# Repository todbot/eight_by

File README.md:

# eight_by

An 8-knob + 8 buttons + eight RGB LEDs board,<br/>
all controllable with only 8 pins

Pot options:

- 9mm Song Hui trimmer pots B10K - [synthcube](https://synthcube.com/cart/parts/potentiometers-and-trimpots/song-huei-9mm-panel-trim-pot-short)
- Just about any other 9mm pot

Buttons are: 
- 12mm tact (LCSC C561260)

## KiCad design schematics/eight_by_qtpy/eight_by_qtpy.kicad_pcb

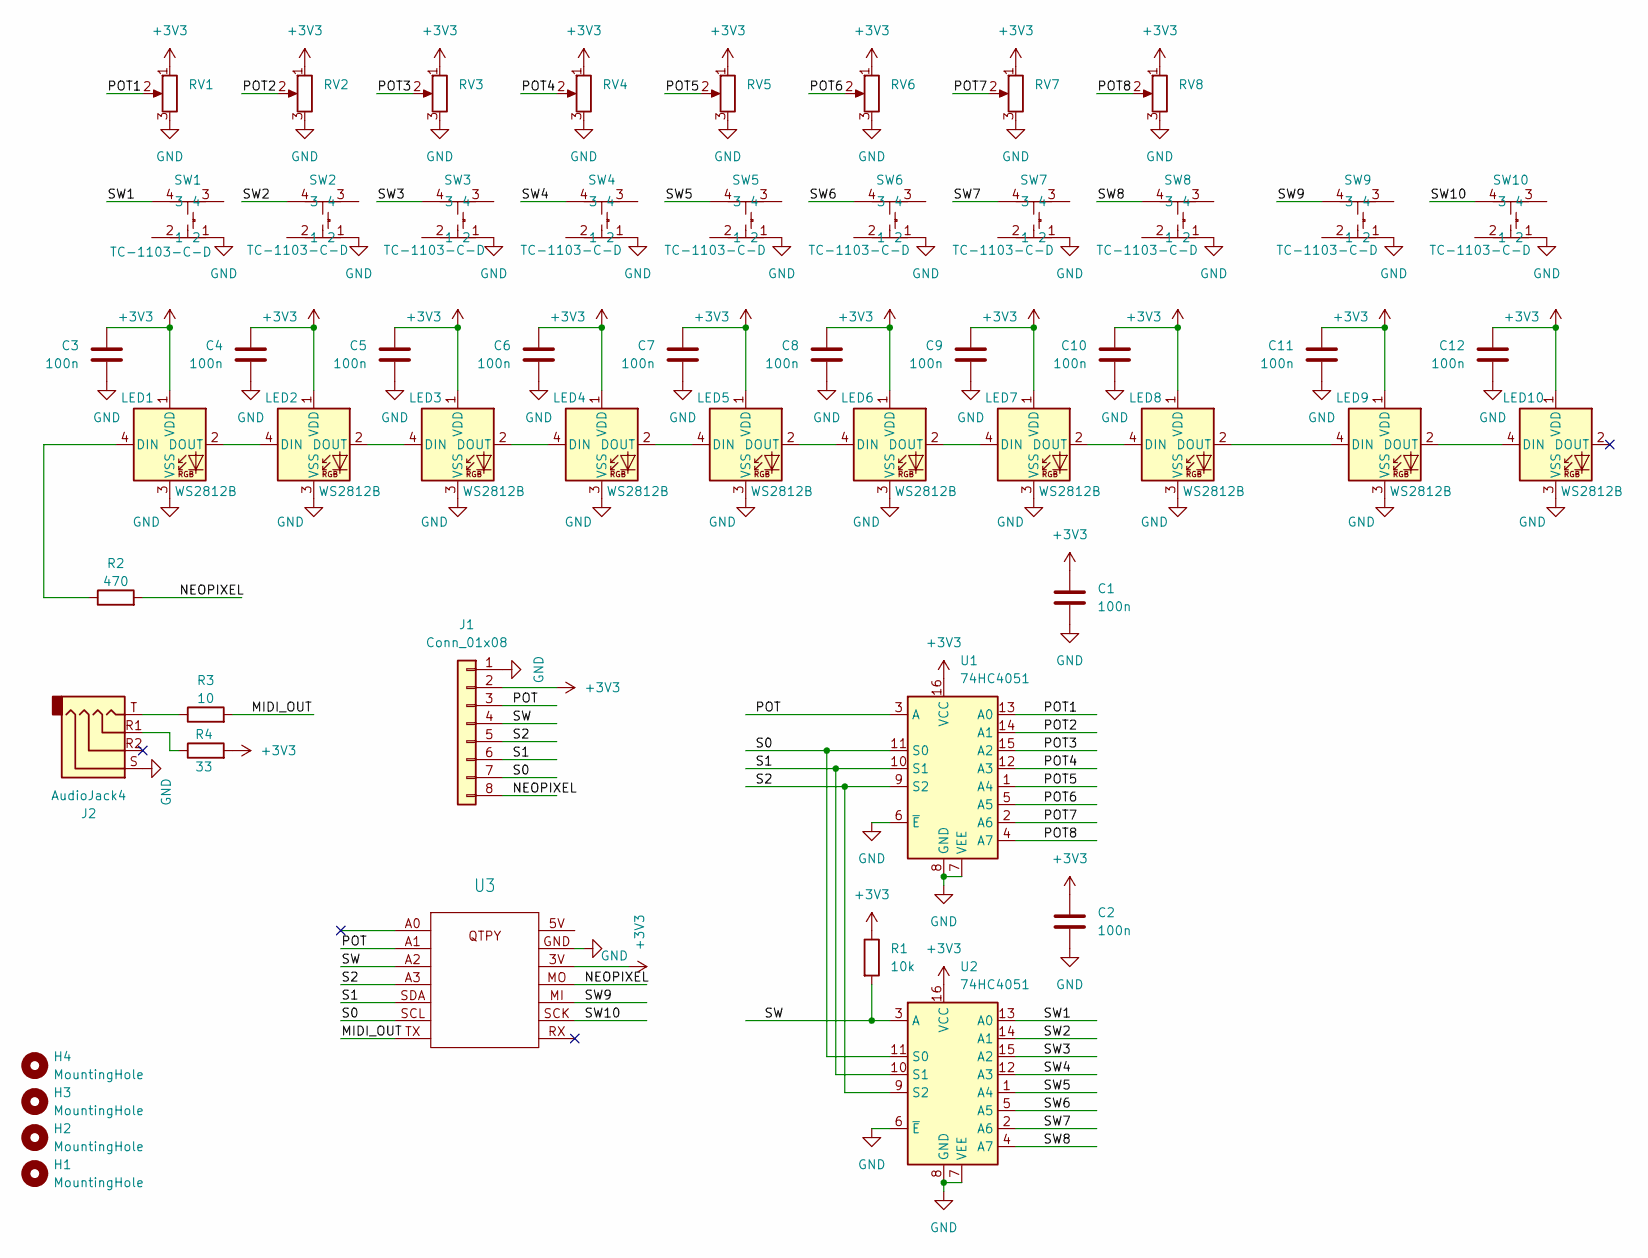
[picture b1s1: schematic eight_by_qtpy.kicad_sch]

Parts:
C1, C2, C3, C4, C5, C6, C7, C8, C9, C10, C11, C12: 100n; C_0603_1608Metric
H1, H2, H3, H4: MountingHole; MountingHole_2.5mm
J1: Conn_01x08; PinHeader_1x08_P2.54mm_Vertical
J2: AudioJack4; Jack_3.5mm_PJ320D_Horizontal
LED1, LED2, LED3, LED4, LED5, LED6, LED7, LED8, LED9, LED10: WS2812B; LED_WS2812B-Mini_PLCC4_3.5x3.5mm
R1: 10k; R_0603_1608Metric
R2: 470; R_0603_1608Metric
R3: 10; R_0603_1608Metric
R4: 33; R_0603_1608Metric
RV1, RV2, RV3, RV4, RV5, RV6, RV7, RV8: R_Potentiometer; Potentiometer_Alps_RK09K_Single_Vertical
SW1, SW2, SW3, SW4, SW5, SW6, SW7, SW8, SW9, SW10: TC-1103-C-D; SW-TH_4P-L12.0-W12.0-P5.00-LS12.5; LCSC Part C561260
U1, U2: 74HC4051; SOIC-16_3.9x9.9mm_P1.27mm
U3: QTPY_TH_HEADERSOCKET

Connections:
+3V3: C1.1, C2.1, C3.1, C4.1, C5.1, C6.1, C7.1, C8.1, C9.1, C10.1, C11.1, C12.1, J1.2, LED1.1 (VDD), LED2.1 (VDD), LED3.1 (VDD), LED4.1 (VDD), LED5.1 (VDD), LED6.1 (VDD), LED7.1 (VDD), LED8.1 (VDD), LED9.1 (VDD), LED10.1 (VDD), R1.1, R4.2, RV1.1, RV2.1, RV3.1, RV4.1, RV5.1, RV6.1, RV7.1, RV8.1, U1.16 (VCC), U2.16 (VCC), U3.3V
/MIDI_OUT: R3.2, U3.TX
/NEOPIXEL: J1.8, R2.2, U3.MO
/POT: J1.3, U1.3 (A), U3.A1 (9)
/POT1: RV1.2, U1.13 (A0)
/POT2: RV2.2, U1.14 (A1)
/POT3: RV3.2, U1.15 (A2)
/POT4: RV4.2, U1.12 (A3)
/POT5: RV5.2, U1.1 (A4)
/POT6: RV6.2, U1.5 (A5)
/POT7: RV7.2, U1.2 (A6)
/POT8: RV8.2, U1.4 (A7)
/S0: J1.7, U1.11 (S0), U2.11 (S0), U3.SCL
/S1: J1.6, U1.10 (S1), U2.10 (S1), U3.SDA
/S2: J1.5, U1.9 (S2), U2.9 (S2), U3.A3
/SW: J1.4, R1.2, U2.3 (A), U3.A2
/SW1: SW1.4, U2.13 (A0)
/SW2: SW2.4, U2.14 (A1)
/SW3: SW3.4, U2.15 (A2)
/SW4: SW4.4, U2.12 (A3)
/SW5: SW5.4, U2.1 (A4)
/SW6: SW6.4, U2.5 (A5)
/SW7: SW7.4, U2.2 (A6)
/SW8: SW8.4, U2.4 (A7)
/SW9: SW9.4, U3.MI
/SW10: SW10.4, U3.SCK
GND: C1.2, C2.2, C3.2, C4.2, C5.2, C6.2, C7.2, C8.2, C9.2, C10.2, C11.2, C12.2, J1.1, J2.S, LED1.3 (VSS), LED2.3 (VSS), LED3.3 (VSS), LED4.3 (VSS), LED5.3 (VSS), LED6.3 (VSS), LED7.3 (VSS), LED8.3 (VSS), LED9.3 (VSS), LED10.3 (VSS), RV1.3, RV2.3, RV3.3, RV4.3, RV5.3, RV6.3, RV7.3, RV8.3, SW1.1, SW2.1, SW3.1, SW4.1, SW5.1, SW6.1, SW7.1, SW8.1, SW9.1, SW10.1, U1.6 (~E), U1.7 (VEE), U1.8 (GND), U2.6 (~E), U2.7 (VEE), U2.8 (GND), U3.GND (14)
unnamed: J2.R1, R4.1
unnamed: J2.T, R3.1
unnamed: LED1.4 (DIN), R2.1
unnamed: LED1.2 (DOUT), LED2.4 (DIN)
unnamed: LED2.2 (DOUT), LED3.4 (DIN)
unnamed: LED3.2 (DOUT), LED4.4 (DIN)
unnamed: LED4.2 (DOUT), LED5.4 (DIN)
unnamed: LED5.2 (DOUT), LED6.4 (DIN)
unnamed: LED6.2 (DOUT), LED7.4 (DIN)
unnamed: LED7.2 (DOUT), LED8.4 (DIN)
unnamed: LED8.2 (DOUT), LED9.4 (DIN)
unnamed: LED9.2 (DOUT), LED10.4 (DIN)

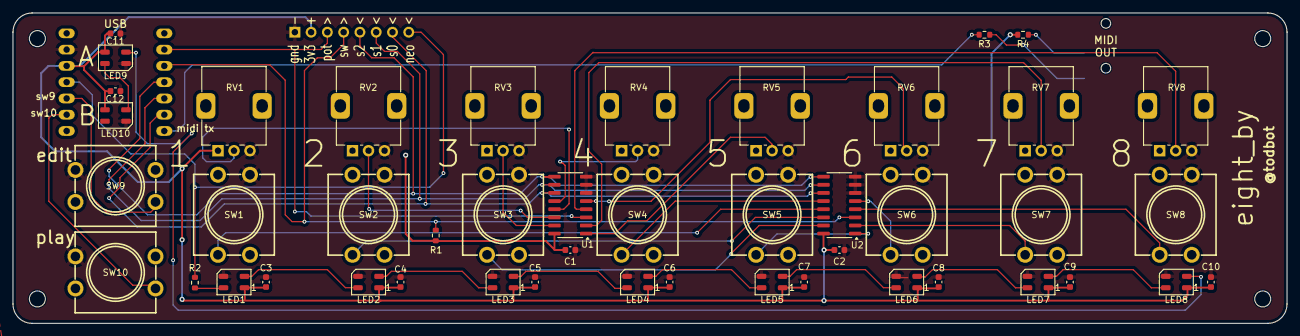
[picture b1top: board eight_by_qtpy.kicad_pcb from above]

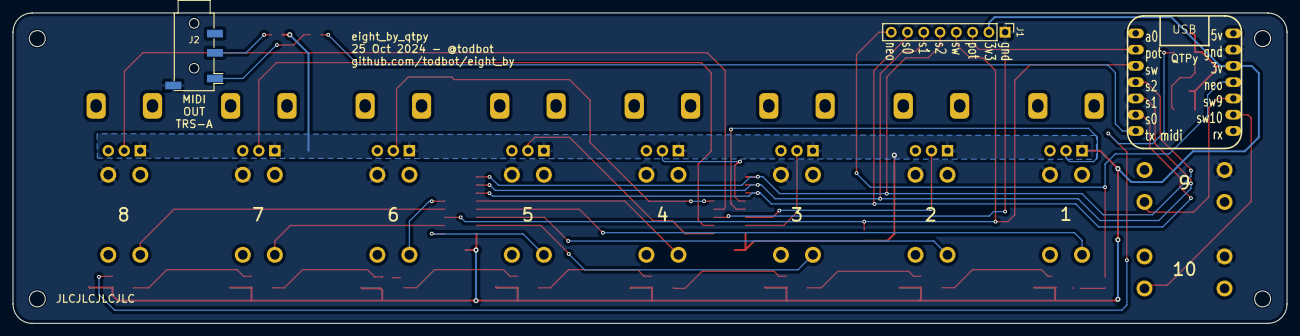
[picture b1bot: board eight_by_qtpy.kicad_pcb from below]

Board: 2 copper layers, 198.9 x 48.4 mm, 53 parts (3 on the bottom side), 39 nets.

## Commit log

2024-05-30 first
2024-06-27 pcb silkscren update
2024-10-23 add render
2024-10-24 eight_by_qtpy idea
2024-10-24 add two extra buttons & LEDs if using a QTpy
2024-10-26 clean up
2024-11-14 rethinking eight_by_qtpy
2024-11-23 new silkscreen
2024-11-24 refactor eight_by_qtpy to use 12mm switches instead of std 6mm tact
2024-11-25 clea up eight_by_qtpy refactor layout
2024-11-25 clean up eight_by_qtpy refactor layout
2024-11-26 files as sent to fab
2025-06-04 add sch pdf
2025-06-04 add sch png
2025-06-04 sch in readme
2025-06-04 add eight_by_qtpy render
